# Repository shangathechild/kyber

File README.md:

# Kyber
An argb controller for Personal computers
I made this as my JRGB pins on my motherboard doesnt work properly. It could also be modified to support a greater number of ARGB headers.

### Features:
- It has 4 ARGB headers
- It has 1 4 pin molex power connector for a Peripheral connector which connects to the PSU

## PCB:
### Schematic:

### PCB:

## CAD

## Important notes:
- It takes up 15mm of width behind your computer
- You have to bend the Bulk capacitors legs to make it fit

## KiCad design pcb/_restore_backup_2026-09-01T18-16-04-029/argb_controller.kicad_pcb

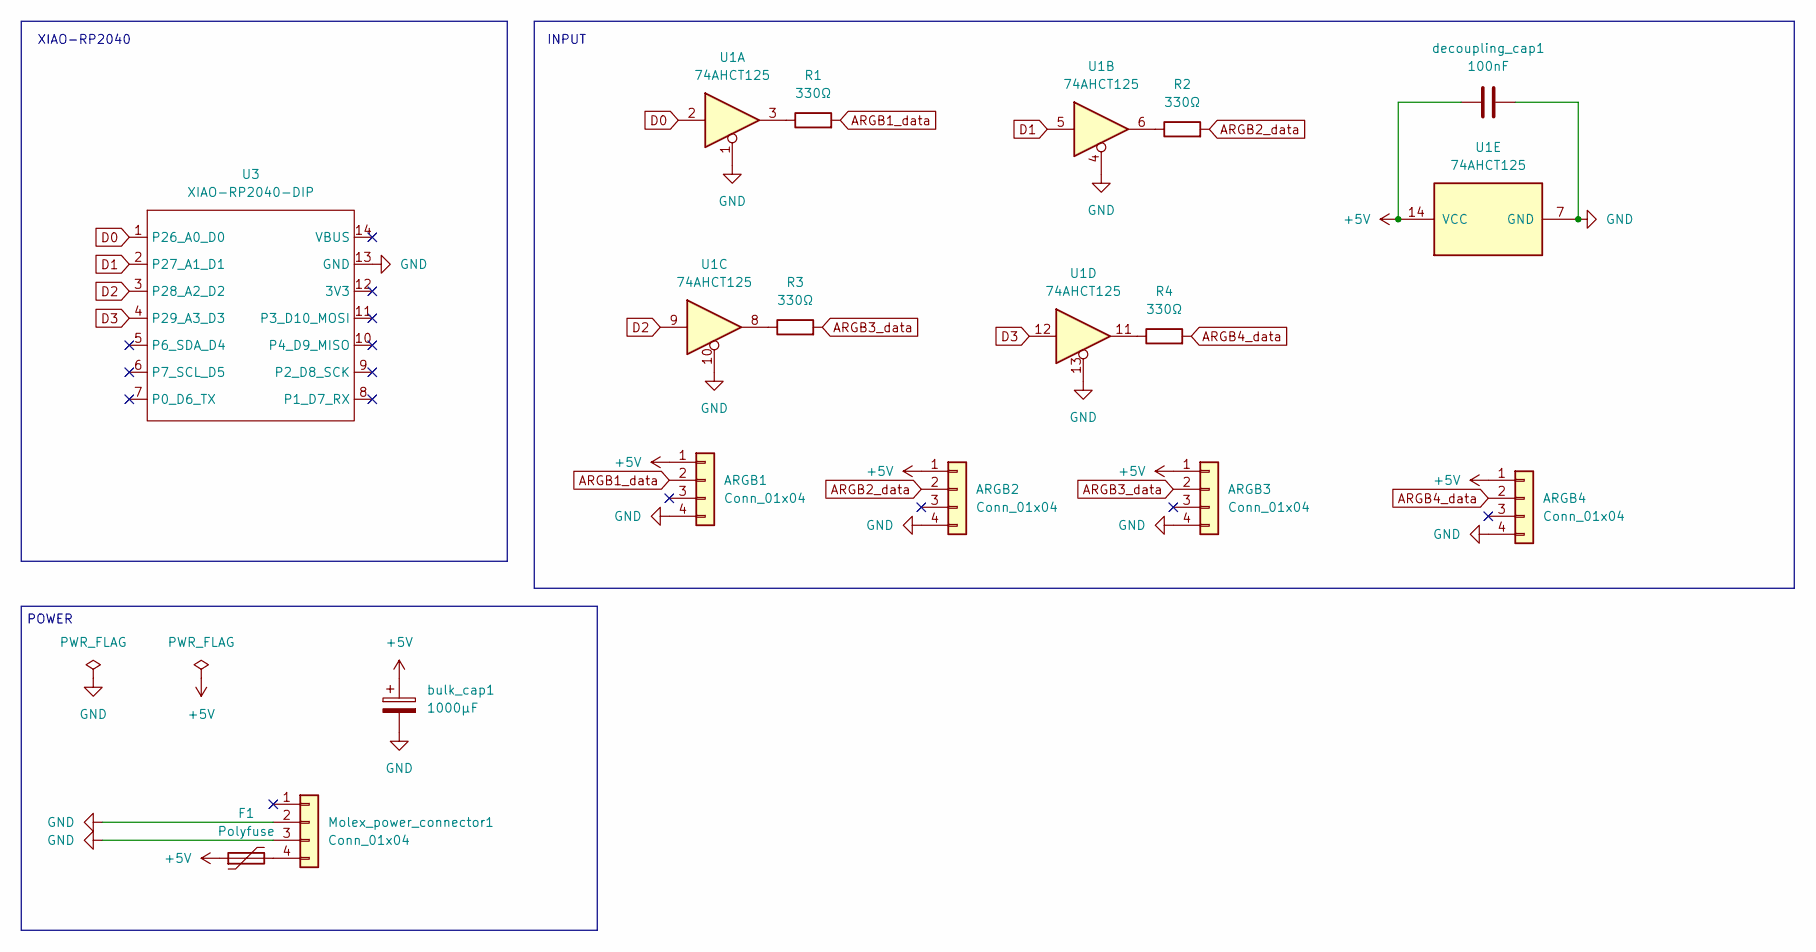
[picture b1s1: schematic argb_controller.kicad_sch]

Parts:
ARGB1, ARGB2, ARGB3, ARGB4: Conn_01x04; PinHeader_1x04_P2.54mm_Horizontal
F1: Polyfuse; FUS_RHEF100_TYCO_TYC
Molex_power_connector1: Conn_01x04; PWR_Molex_4pin_P5.08mm_Horizontal
R1, R2, R3, R4: 330Ω; R_Axial_DIN0207_L6.3mm_D2.5mm_P10.16mm_Horizontal
U1: 74AHCT125; DIP-14_W7.62mm_LongPads
U3: XIAO-RP2040-DIP
bulk_cap1: 1000µF; CP_Radial_D10.0mm_P5.00mm
decoupling_cap1: 100nF; C_Rect_L7.2mm_W2.5mm_P5.00mm

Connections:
+5V: ARGB1.1, ARGB2.1, ARGB3.1, ARGB4.1, F1.1, U1.14 (VCC), bulk_cap1.1, decoupling_cap1.1
ARGB1_data: ARGB1.2, R1.2
ARGB2_data: ARGB2.2, R2.2
ARGB3_data: ARGB3.2, R3.2
ARGB4_data: ARGB4.2, R4.2
D0: U1.2, U3.1 (P26_A0_D0)
D1: U1.5, U3.2 (P27_A1_D1)
D2: U1.9, U3.3 (P28_A2_D2)
D3: U1.12, U3.4 (P29_A3_D3)
GND: ARGB1.4, ARGB2.4, ARGB3.4, ARGB4.4, Molex_power_connector1.2, Molex_power_connector1.3, U1.1, U1.4, U1.7 (GND), U1.10, U1.13, U3.13 (GND), bulk_cap1.2, decoupling_cap1.2
unnamed: F1.2, Molex_power_connector1.4
unnamed: R1.1, U1.3
unnamed: R2.1, U1.6
unnamed: R3.1, U1.8
unnamed: R4.1, U1.11

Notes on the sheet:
INPUT
XIAO-RP2040
POWER

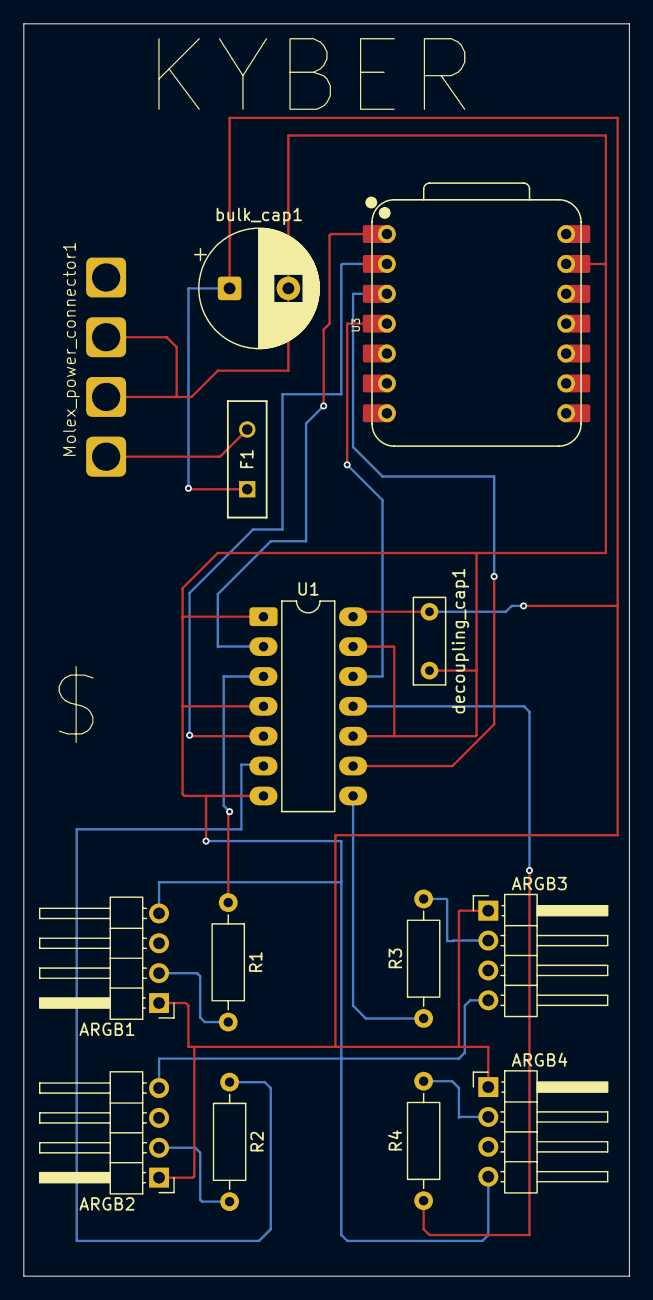
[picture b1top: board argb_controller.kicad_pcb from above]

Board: 2 copper layers, 51.5 x 106.5 mm, 14 parts (0 on the bottom side), 15 nets.
